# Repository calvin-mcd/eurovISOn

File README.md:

# eurovISOn
 
40% keyboard designed by some weird Europeans from the 40s discord. It's a qaz-like with special character cluster, exploded ISO with rgb (because why not!?), a macro column to the left and rotary and oled support. It sports a rp2040 and uses a pico Daughterboard for the usb port.

The case is being designed by Haizeus from [haikey](https://www.haikey.design/) and is inspired by the float65. Case design is not finished.

Disclaimer: 
**this is a work in progress project, do not use any of its files**

## Layout

[Link](https://www.keyboard-layout-editor.com/#/gists/c5cb8d03115bd811b00f9896965940d2)
**the KLE gist is outdated, refer to the screen above**

## Pictures

## Todo

- [ ] make fresh gerber files & bom, pos
- [ ] make firmeware
- [ ] order and test proto pcbs
- [ ] finish case design
- [ ] order and test proto case

## Disclaimer

Please note that this project is a work in progress with no guarantees of a working outcome. No-one involved in this project is responsible for any usage issues that may arise. However, feel free to edit, modify and otherwise utilise these files.

## License

This project is released under the GPL v3 License. Please refer to the LICENCE file.

## Credits
	
As always big thanks to the many people who helped me and inspired this board!

Any questions, contact Calvin0563 on Discord.

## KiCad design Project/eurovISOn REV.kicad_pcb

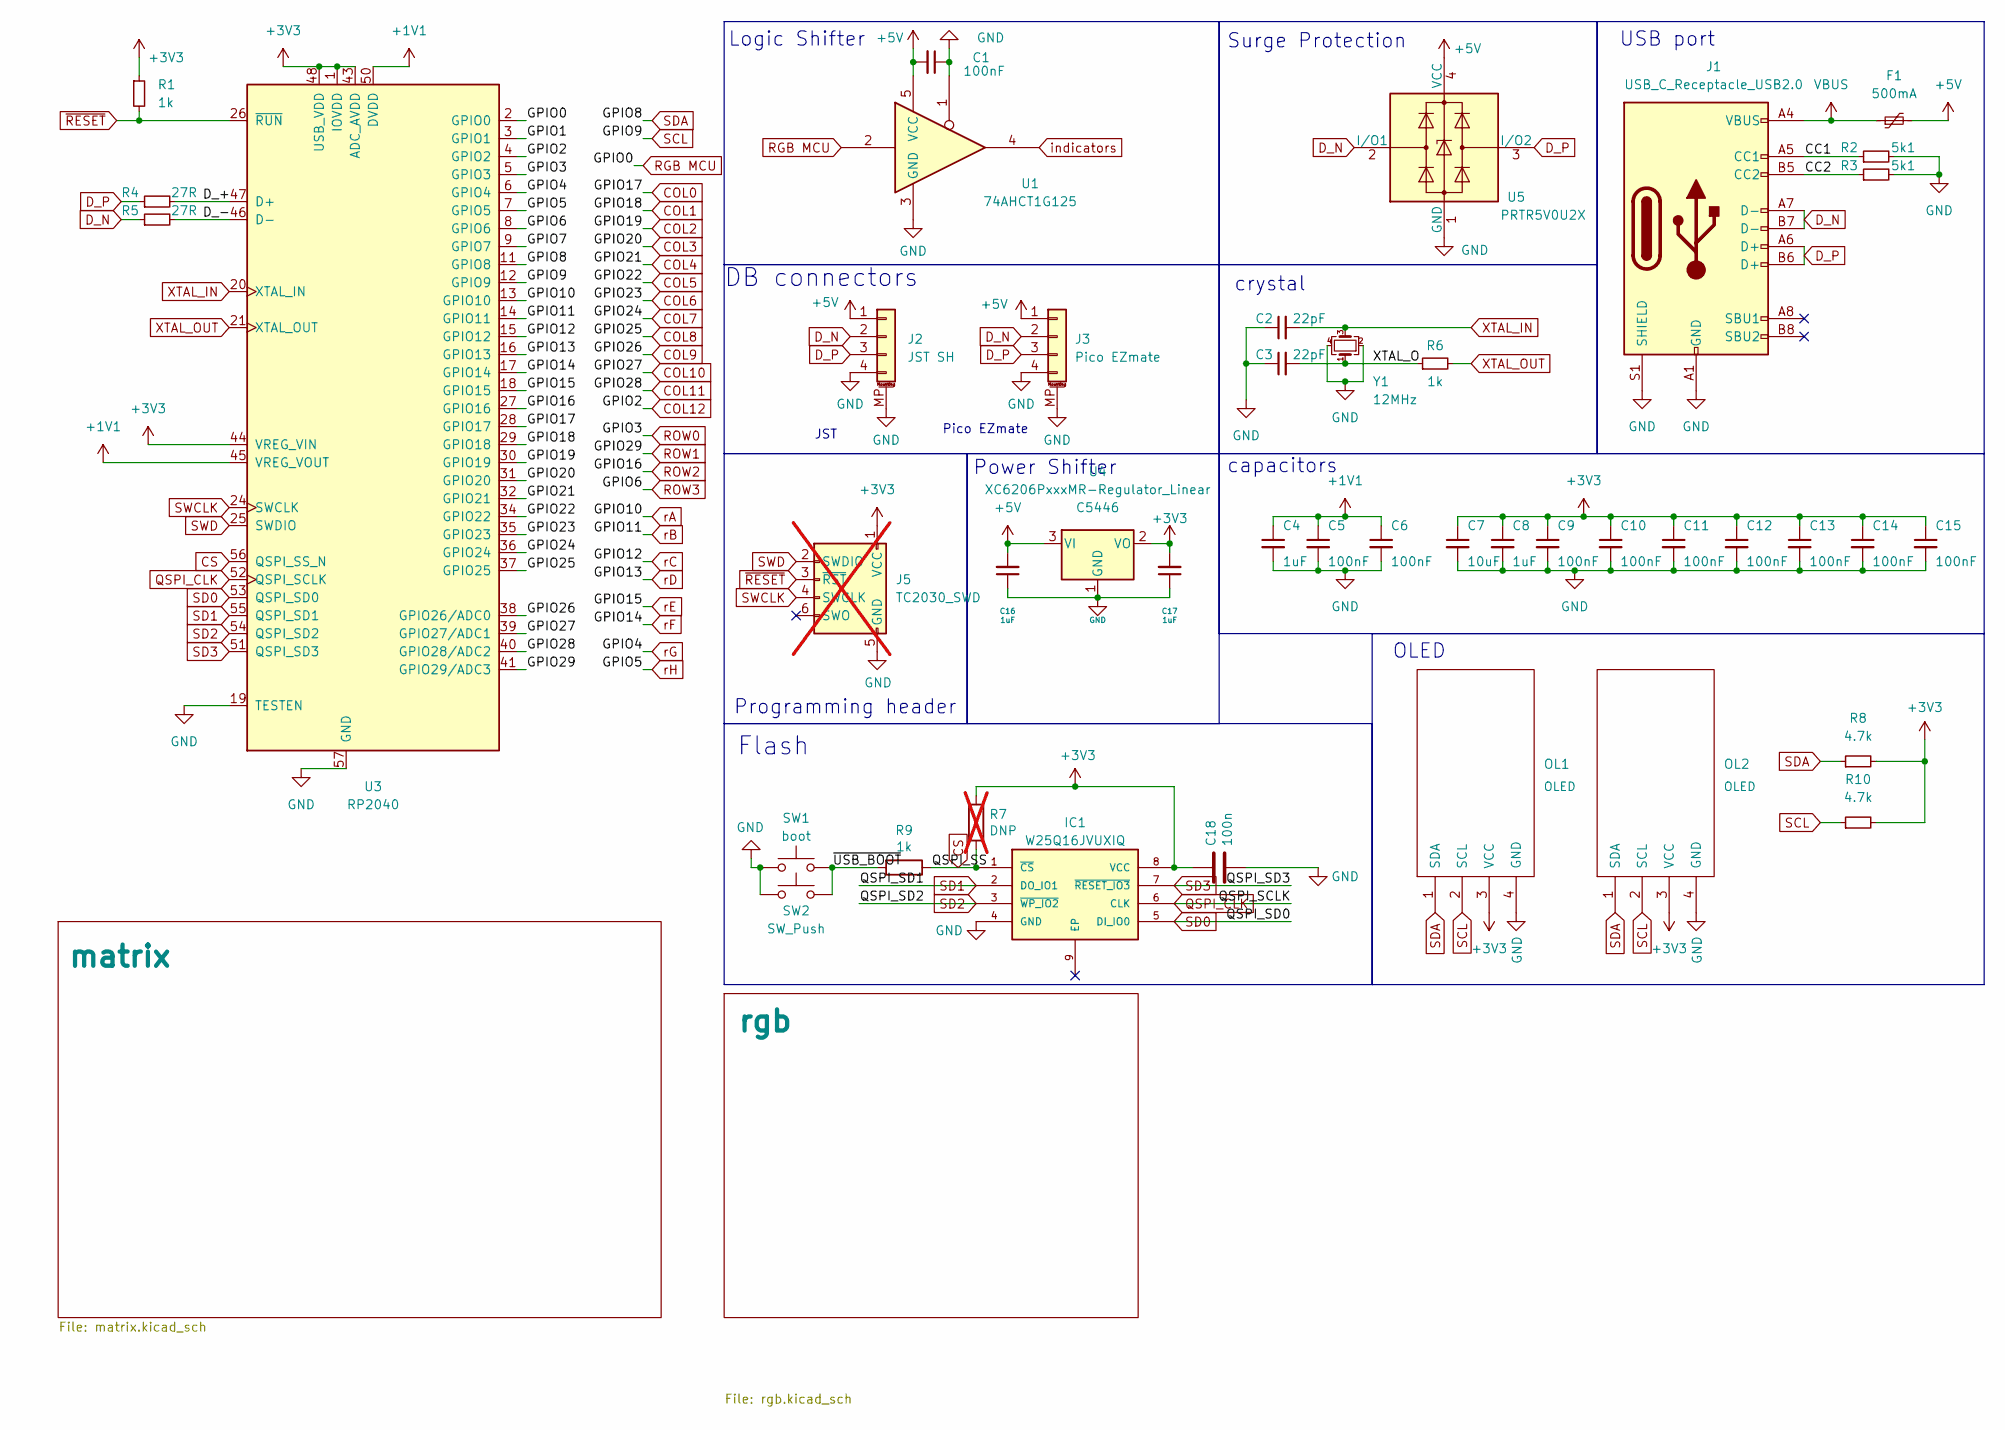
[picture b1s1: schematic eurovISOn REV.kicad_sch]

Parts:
C1: 100nF; C_0402_1005Metric
C2, C3: 22pF; C_0402_1005Metric; LCSC C1555
C4, C8, C16, C17: 1uF; C_0402_1005Metric; LCSC C52923
C5, C6, C9, C10, C11, C12, C13, C14, C15: 100nF; C_0402_1005Metric; LCSC C1525
C7: 10uF; C_0402_1005Metric; LCSC C15525
C18: 100n; C_0402_1005Metric; LCSC C1525
F1: 500mA; Fuse_1206_3216Metric; LCSC C70076
IC1: W25Q16JVUXIQ; SON50P300X200X60-9N; MANUFACTURER_PART_NUMBER W25Q16JVUXIQ; LCSC Part C2843335
J1: USB_C_Receptacle_USB2.0; USB_C_Receptacle_HRO_TYPE-C-31-M-12; LCSC C165948
J2: JST SH; JST_SH_SM04B-SRSS-TB_1x04-1MP_P1.00mm_Horizontal
J3: Pico EZmate; Molex_Pico-EZmate_78171-0004_1x04-1MP_P1.20mm_Vertical
J5: TC2030_SWD; CON_TC2030_outlined; not fitted
OL1, OL2: OLED; OLED_v2
R1, R6: 1k; R_0402_1005Metric; LCSC C11702
R2, R3: 5k1; R_0402_1005Metric; LCSC C25905
R4, R5: 27R; R_0402_1005Metric; LCSC C25190
R7: DNP; C_0402_1005Metric; LCSC C25905; not fitted
R8, R10: 4.7k; R_0402_1005Metric; LCSC C25900
R9: 1k; R_0402_1005Metric; LCSC Part C25543
SW1: boot; SW_SPST_TL3342; LCSC Part C115351
SW2: SW_Push; PinSocket_1x02_P2.54mm_Vertical
U1: 74AHCT1G125; TSOT-23-5
U3: RP2040; RP2040-QFN-56; LCSC C2040
U4: XC6206PxxxMR-Regulator_Linear; SOT-23; LCSC C5446
U5: PRTR5V0U2X; SOT-143; LCSC C2827688
Y1: 12MHz; Crystal_SMD_3225-4Pin_3.2x2.5mm; LCSC C9002

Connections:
+1V1: C4.1, C5.1, C6.1, U3.23 (DVDD), U3.45 (VREG_VOUT), U3.50 (DVDD)
+3V3: C7.1, C8.1, C9.1, C10.1, C11.1, C12.1, C13.1, C14.1, C15.1, C17.2, C18.1, IC1.8 (VCC), J5.1 (VCC), OL1.3 (VCC), OL2.3 (VCC), R1.1, R7.1, R8.2, R10.2, U3.1 (IOVDD), U3.10 (IOVDD), U3.22 (IOVDD), U3.33 (IOVDD), U3.42 (IOVDD), U3.43 (ADC_AVDD), U3.44 (VREG_VIN), U3.48 (USB_VDD), U3.49 (IOVDD), U4.2 (VO)
+5V: C1.2, C16.2, F1.2, J2.1, J3.1, U1.5 (VCC), U4.3 (VI), U5.4 (VCC); also elsewhere on the board
/CC1: J1.A5 (CC1), R2.1
/CC2: J1.B5 (CC2), R3.1
/D_+: R4.2, U3.47 (D+)
/D_-: R5.2, U3.46 (D-)
/GPIO1: U3.3 (GPIO1)
/GPIO7: U3.9 (GPIO7)
/XTAL_O: C3.2, R6.1, Y1.1
/~USB_BOOT: R9.2, SW1.2, SW2.2
COL0: U3.28 (GPIO17); also elsewhere on the board
COL1: U3.29 (GPIO18); also elsewhere on the board
COL2: U3.30 (GPIO19); also elsewhere on the board
COL3: U3.31 (GPIO20); also elsewhere on the board
COL4: U3.32 (GPIO21); also elsewhere on the board
COL5: U3.34 (GPIO22); also elsewhere on the board
COL6: U3.35 (GPIO23); also elsewhere on the board
COL7: U3.36 (GPIO24); also elsewhere on the board
COL8: U3.37 (GPIO25); also elsewhere on the board
COL9: U3.38 (GPIO26/ADC0); also elsewhere on the board
COL10: U3.39 (GPIO27/ADC1); also elsewhere on the board
COL11: U3.40 (GPIO28/ADC2); also elsewhere on the board
COL12: U3.4 (GPIO2); also elsewhere on the board
CS: IC1.1 (~CS), R7.2, R9.1, U3.56 (QSPI_SS_N)
D_N: J1.A7 (D-), J1.B7 (D-), J2.2, J3.2, R5.1, U5.2 (I/O1)
D_P: J1.A6 (D+), J1.B6 (D+), J2.3, J3.3, R4.1, U5.3 (I/O2)
GND: C1.1, C2.1, C3.1, C4.2, C5.2, C6.2, C7.2, C8.2, C9.2, C10.2, C11.2, C12.2, C13.2, C14.2, C15.2, C16.1, C17.1, C18.2, IC1.4 (GND), J1.A1 (GND), J1.A12 (GND), J1.B1 (GND), J1.B12 (GND), J1.S1 (SHIELD), J2.4, J2.MP (MountPin), J3.4, J3.MP (MountPin), J5.5 (GND), OL1.4 (GND), OL2.4 (GND), R2.2, R3.2, SW1.1, SW2.1, U1.1, U1.3 (GND), U3.19 (TESTEN), U3.57 (GND), U4.1 (GND), U5.1 (GND), Y1.2, Y1.4; also elsewhere on the board
QSPI_CLK: IC1.6 (CLK), U3.52 (QSPI_SCLK)
RGB MCU: U1.2, U3.2 (GPIO0)
ROW0: U3.5 (GPIO3); also elsewhere on the board
ROW1: U3.41 (GPIO29/ADC3); also elsewhere on the board
ROW2: U3.27 (GPIO16); also elsewhere on the board
ROW3: U3.8 (GPIO6); also elsewhere on the board
SCL: OL1.2 (SCL), OL2.2 (SCL), R10.1, U3.12 (GPIO9)
SD0: IC1.5 (DI_IO0), U3.53 (QSPI_SD0)
SD1: IC1.2 (DO_IO1), U3.55 (QSPI_SD1)
SD2: IC1.3 (~WP_IO2), U3.54 (QSPI_SD2)
SD3: IC1.7 (~RESET_IO3), U3.51 (QSPI_SD3)
SDA: OL1.1 (SDA), OL2.1 (SDA), R8.1, U3.11 (GPIO8)
SWCLK: J5.4 (SWCLK), U3.24 (SWCLK)
SWD: J5.2 (SWDIO), U3.25 (SWDIO)
VBUS: F1.1, J1.A4 (VBUS), J1.A9 (VBUS), J1.B4 (VBUS), J1.B9 (VBUS)
XTAL_IN: C2.2, U3.20 (XTAL_IN), Y1.3
XTAL_OUT: R6.2, U3.21 (XTAL_OUT)
indicators: U1.4; also elsewhere on the board
rA: U3.13 (GPIO10); also elsewhere on the board
rB: U3.14 (GPIO11); also elsewhere on the board
rC: U3.15 (GPIO12); also elsewhere on the board
rD: U3.16 (GPIO13); also elsewhere on the board
rE: U3.18 (GPIO15); also elsewhere on the board
rF: U3.17 (GPIO14); also elsewhere on the board
rG: U3.6 (GPIO4); also elsewhere on the board
rH: U3.7 (GPIO5); also elsewhere on the board
~RESET: J5.3 (~RST), R1.2, U3.26 (~RUN)

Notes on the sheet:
capacitors
Power Shifter
Pico EZmate
OLED
crystal
Logic Shifter
DB connectors
USB port
Flash
Programming header
JST
Surge Protection

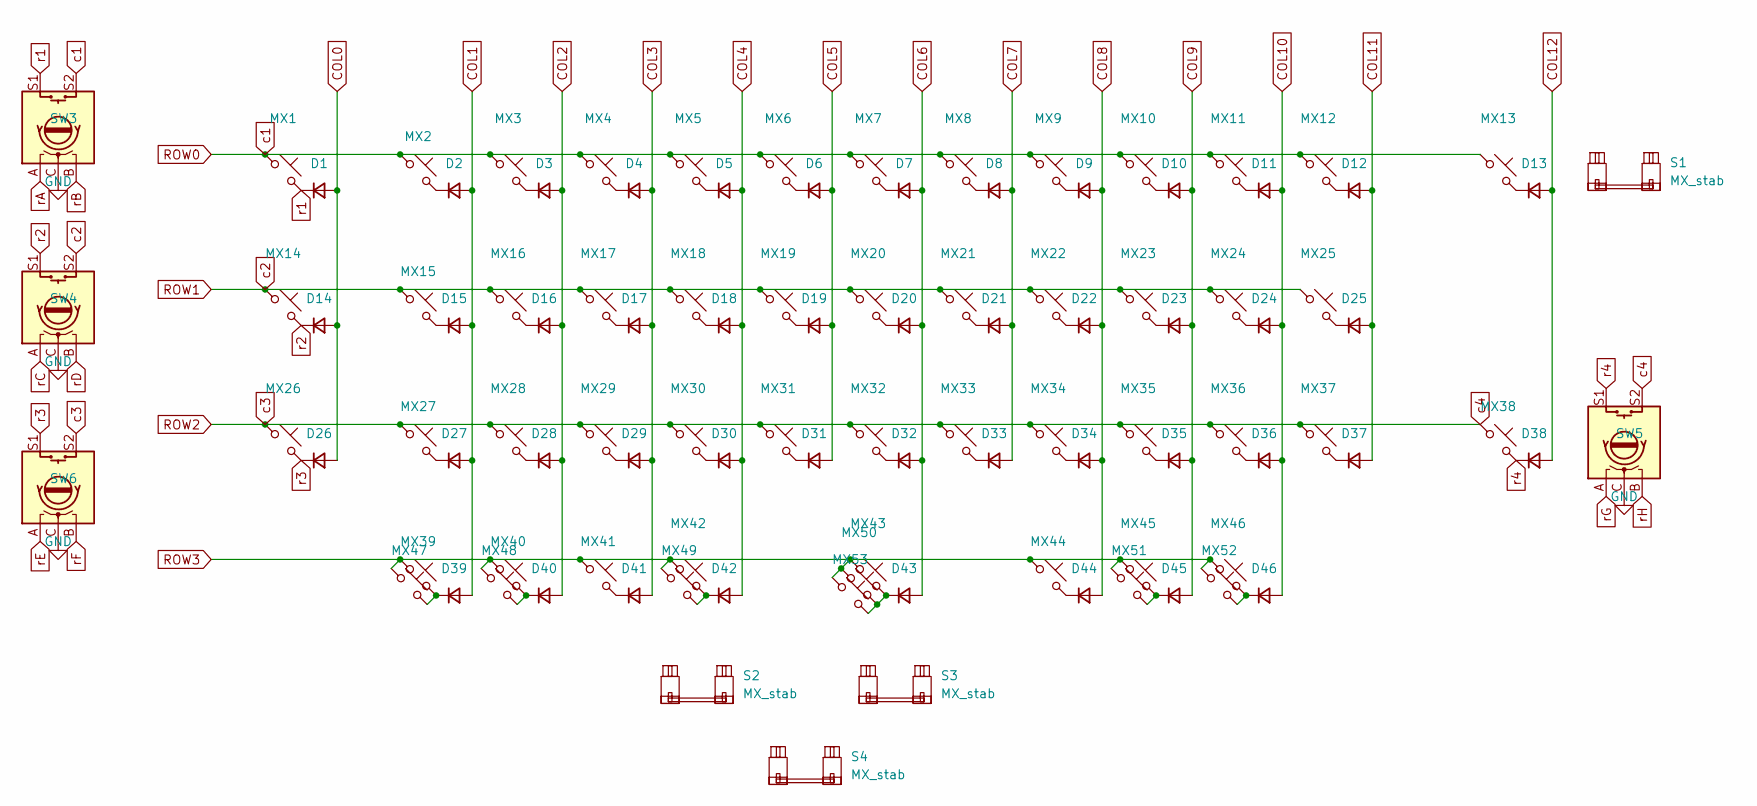
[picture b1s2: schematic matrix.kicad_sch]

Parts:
D1, D2, D3, D4, D5, D6, D7, D8, D9, D10, D11, D12, D13, D14, D15, D16, D17, D18, D19, D20, D21, D22, D23, D24, D25, D26, D27, D28, D29, D30, D31, D32, D33, D34, D35, D36, D37, D38, D39, D40, D41, D42, D43, D44, D45, D46: D_Small; D_SOD-123F
MX1, MX2, MX3, MX4, MX5, MX6, MX7, MX8, MX9, MX10, MX11, MX12, MX13, MX14, MX16, MX17, MX18, MX19, MX20, MX21, MX22, MX23, MX24, MX25, MX26, MX28, MX29, MX30, MX31, MX32, MX33, MX34, MX35, MX36, MX37, MX38, MX40, MX46, MX47, MX49, MX50, MX51, MX53: MX_SW_HS; SW_MX_1u
MX15, MX39, MX41, MX44, MX45, MX48, MX52: MX_SW_HS; SW_MX_1.25u
MX27, MX42, MX43: MX_SW_HS; SW_MX_1.75u
S1: MX_stab; STAB_MX_P_ISO-ROT
S2, S3: MX_stab; STAB_MX_P_3u
S4: MX_stab; STAB_MX_P_6u
SW3, SW4, SW5, SW6: RotaryEncoder_Switch; ROT_Alps_EC11E-Switch

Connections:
COL0: D1.2 (A), D14.2 (A), D26.2 (A); also elsewhere on the board
COL1: D2.2 (A), D15.2 (A), D27.2 (A), D39.2 (A); also elsewhere on the board
COL2: D3.2 (A), D16.2 (A), D28.2 (A), D40.2 (A); also elsewhere on the board
COL3: D4.2 (A), D17.2 (A), D29.2 (A), D41.2 (A); also elsewhere on the board
COL4: D5.2 (A), D18.2 (A), D30.2 (A), D42.2 (A); also elsewhere on the board
COL5: D6.2 (A), D19.2 (A), D31.2 (A); also elsewhere on the board
COL6: D7.2 (A), D20.2 (A), D32.2 (A), D43.2 (A); also elsewhere on the board
COL7: D8.2 (A), D21.2 (A), D33.2 (A); also elsewhere on the board
COL8: D9.2 (A), D22.2 (A), D34.2 (A), D44.2 (A); also elsewhere on the board
COL9: D10.2 (A), D23.2 (A), D35.2 (A), D45.2 (A); also elsewhere on the board
COL10: D11.2 (A), D24.2 (A), D36.2 (A), D46.2 (A); also elsewhere on the board
COL11: D12.2 (A), D25.2 (A), D37.2 (A); also elsewhere on the board
COL12: D13.2 (A), D38.2 (A); also elsewhere on the board
GND: SW3.C, SW4.C, SW5.C, SW6.C; also elsewhere on the board
unnamed: D2.1 (K), MX2.2
unnamed: D3.1 (K), MX3.2
unnamed: D4.1 (K), MX4.2
unnamed: D5.1 (K), MX5.2
unnamed: D6.1 (K), MX6.2
unnamed: D7.1 (K), MX7.2
unnamed: D8.1 (K), MX8.2
unnamed: D9.1 (K), MX9.2
unnamed: D10.1 (K), MX10.2
unnamed: D11.1 (K), MX11.2
unnamed: D12.1 (K), MX12.2
unnamed: D13.1 (K), MX13.2
unnamed: D15.1 (K), MX15.2
unnamed: D16.1 (K), MX16.2
unnamed: D17.1 (K), MX17.2
unnamed: D18.1 (K), MX18.2
unnamed: D19.1 (K), MX19.2
unnamed: D20.1 (K), MX20.2
unnamed: D21.1 (K), MX21.2
unnamed: D22.1 (K), MX22.2
unnamed: D23.1 (K), MX23.2
unnamed: D24.1 (K), MX24.2
unnamed: D25.1 (K), MX25.2
unnamed: D27.1 (K), MX27.2
unnamed: D28.1 (K), MX28.2
unnamed: D29.1 (K), MX29.2
unnamed: D30.1 (K), MX30.2
unnamed: D31.1 (K), MX31.2
unnamed: D32.1 (K), MX32.2
unnamed: D33.1 (K), MX33.2
unnamed: D34.1 (K), MX34.2
unnamed: D35.1 (K), MX35.2
unnamed: D36.1 (K), MX36.2
unnamed: D37.1 (K), MX37.2
unnamed: D39.1 (K), MX39.2, MX47.2
unnamed: D40.1 (K), MX40.2, MX48.2
unnamed: D41.1 (K), MX41.2
unnamed: D42.1 (K), MX42.2, MX49.2
unnamed: D43.1 (K), MX43.2, MX50.2, MX53.2
unnamed: D44.1 (K), MX44.2
unnamed: D45.1 (K), MX45.2, MX51.2
unnamed: D46.1 (K), MX46.2, MX52.2
ROW0: MX1.1, MX2.1, MX3.1, MX4.1, MX5.1, MX6.1, MX7.1, MX8.1, MX9.1, MX10.1, MX11.1, MX12.1, MX13.1, SW3.S2; also elsewhere on the board
ROW1: MX14.1, MX15.1, MX16.1, MX17.1, MX18.1, MX19.1, MX20.1, MX21.1, MX22.1, MX23.1, MX24.1, MX25.1, SW4.S2; also elsewhere on the board
ROW2: MX26.1, MX27.1, MX28.1, MX29.1, MX30.1, MX31.1, MX32.1, MX33.1, MX34.1, MX35.1, MX36.1, MX37.1, MX38.1, SW5.S2, SW6.S2; also elsewhere on the board
ROW3: MX39.1, MX40.1, MX41.1, MX42.1, MX43.1, MX44.1, MX45.1, MX46.1, MX47.1, MX48.1, MX49.1, MX50.1, MX51.1, MX52.1, MX53.1; also elsewhere on the board
r1: D1.1 (K), MX1.2, SW3.S1
r2: D14.1 (K), MX14.2, SW4.S1
r3: D26.1 (K), MX26.2, SW6.S1
r4: D38.1 (K), MX38.2, SW5.S1
rA: SW3.A; also elsewhere on the board
rB: SW3.B; also elsewhere on the board
rC: SW4.A; also elsewhere on the board
rD: SW4.B; also elsewhere on the board
rE: SW6.A; also elsewhere on the board
rF: SW6.B; also elsewhere on the board
rG: SW5.A; also elsewhere on the board
rH: SW5.B; also elsewhere on the board

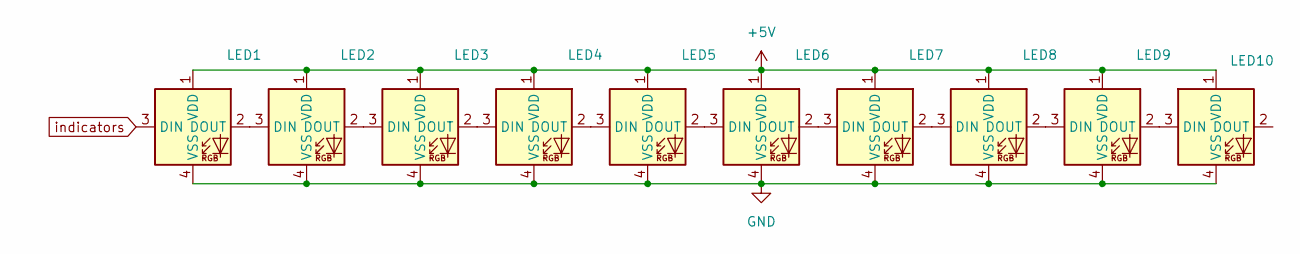
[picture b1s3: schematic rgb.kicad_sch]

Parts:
LED1, LED2, LED3, LED4, LED5, LED6, LED7, LED8, LED9: SK6812MINI-E; LED_6028R
LED10: MX_SK6812MINI-E; LED_MX_6028R

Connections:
+5V: LED1.1 (VDD), LED2.1 (VDD), LED3.1 (VDD), LED4.1 (VDD), LED5.1 (VDD), LED6.1 (VDD), LED7.1 (VDD), LED8.1 (VDD), LED9.1 (VDD), LED10.1 (VDD); also elsewhere on the board
GND: LED1.4 (VSS), LED2.4 (VSS), LED3.4 (VSS), LED4.4 (VSS), LED5.4 (VSS), LED6.4 (VSS), LED7.4 (VSS), LED8.4 (VSS), LED9.4 (VSS), LED10.4 (VSS); also elsewhere on the board
unnamed: LED1.2 (DOUT), LED2.3 (DIN)
unnamed: LED2.2 (DOUT), LED3.3 (DIN)
unnamed: LED3.2 (DOUT), LED4.3 (DIN)
unnamed: LED4.2 (DOUT), LED5.3 (DIN)
unnamed: LED5.2 (DOUT), LED6.3 (DIN)
unnamed: LED6.2 (DOUT), LED7.3 (DIN)
unnamed: LED7.2 (DOUT), LED8.3 (DIN)
unnamed: LED8.2 (DOUT), LED9.3 (DIN)
unnamed: LED9.2 (DOUT), LED10.3 (DIN)
indicators: LED1.3 (DIN); also elsewhere on the board

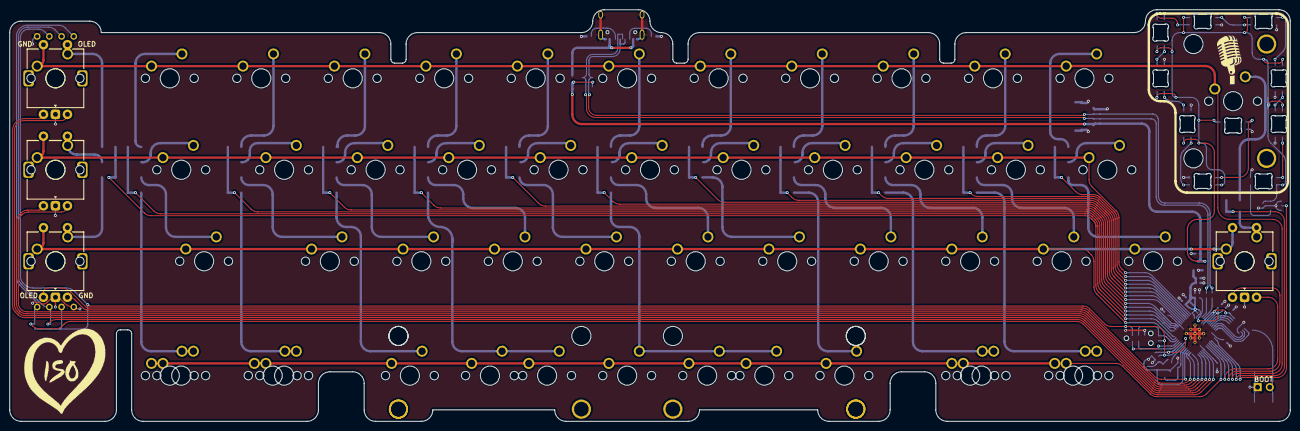
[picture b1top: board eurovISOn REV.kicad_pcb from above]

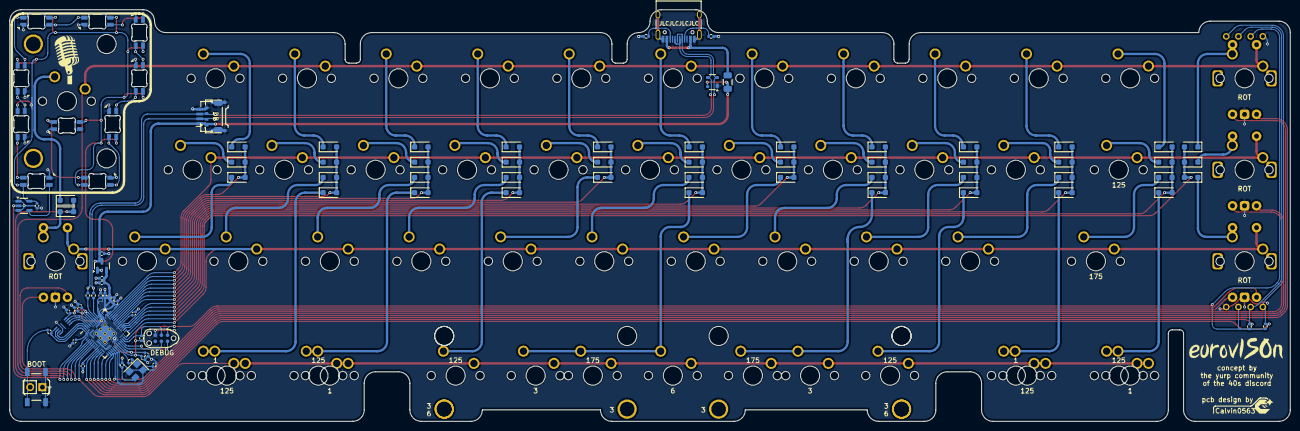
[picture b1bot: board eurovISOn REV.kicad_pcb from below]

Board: 2 copper layers, 266.7 x 85.7 mm, 159 parts (96 on the bottom side), 108 nets.

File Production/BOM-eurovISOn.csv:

Comment,Designator,Footprint,LCSC
boot,SW1,SW_SPST_TL3342,C115351
1k,"R1,R6,R9",R_0402_1005Metric,C11702
100nF,"C1,C10,C11,C12,C13,C14,C15,C18,C5,C6,C9",C_0402_1005Metric,C1525
10uF,C7,C_0402_1005Metric,C15525
22pF,"C2,C3",C_0402_1005Metric,C1555
RP2040,U3,RP2040-QFN-56,C2040
4.7k,"R10,R8",R_0402_1005Metric,C25900
W25Q16JVUXIQ,IC1,SON50P300X200X60-9N,C2843335
27R,"R4,R5",R_0402_1005Metric,C316853
SK6812MINI-E,"LED1,LED10,LED2,LED3,LED4,LED5,LED6,LED7,LED8,LED9",LED_6028R,C5149201
1uF,"C16,C17,C4,C8",C_0402_1005Metric,C52923
XC6206PxxxMR-Regulator_Linear,U4,SOT-23,C5446
Pico EZmate,J3,Molex_Pico-EZmate_78171-0004_1x04-1MP_P1.20mm_Vertical,C588524
D_Small,"D1,D10,D11,D12,D13,D14,D15,D16,D17,D18,D19,D2,D20,D21,D22,D23,D24,D25,D26,D27,D28,D29,D3,D30,D31,D32,D33,D34,D35,D36,D37,D38,D39,D4,D40,D41,D42,D43,D44,D45,D46,D5,D6,D7,D8,D9",D_SOD-123F,C81598
74AHCT1G125,U1,TSOT-23-5,C842287
12MHz,Y1,Crystal_SMD_3225-4Pin_3.2x2.5mm,C9002

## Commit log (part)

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2024-09-30 update project
2024-11-02 final revision
2025-09-22 backup
2025-11-23 rev wip
    usb port added
2026-03-22 readme update
2026-03-24 gerbers
2026-04-11 centered usb port and longer tab for case fitment
2026-04-19 pcb clean up
2026-04-19 kicad 9
2026-05-31 rgb positions
2026-06-10 pcb update
    production files (lacking pos,bom)
